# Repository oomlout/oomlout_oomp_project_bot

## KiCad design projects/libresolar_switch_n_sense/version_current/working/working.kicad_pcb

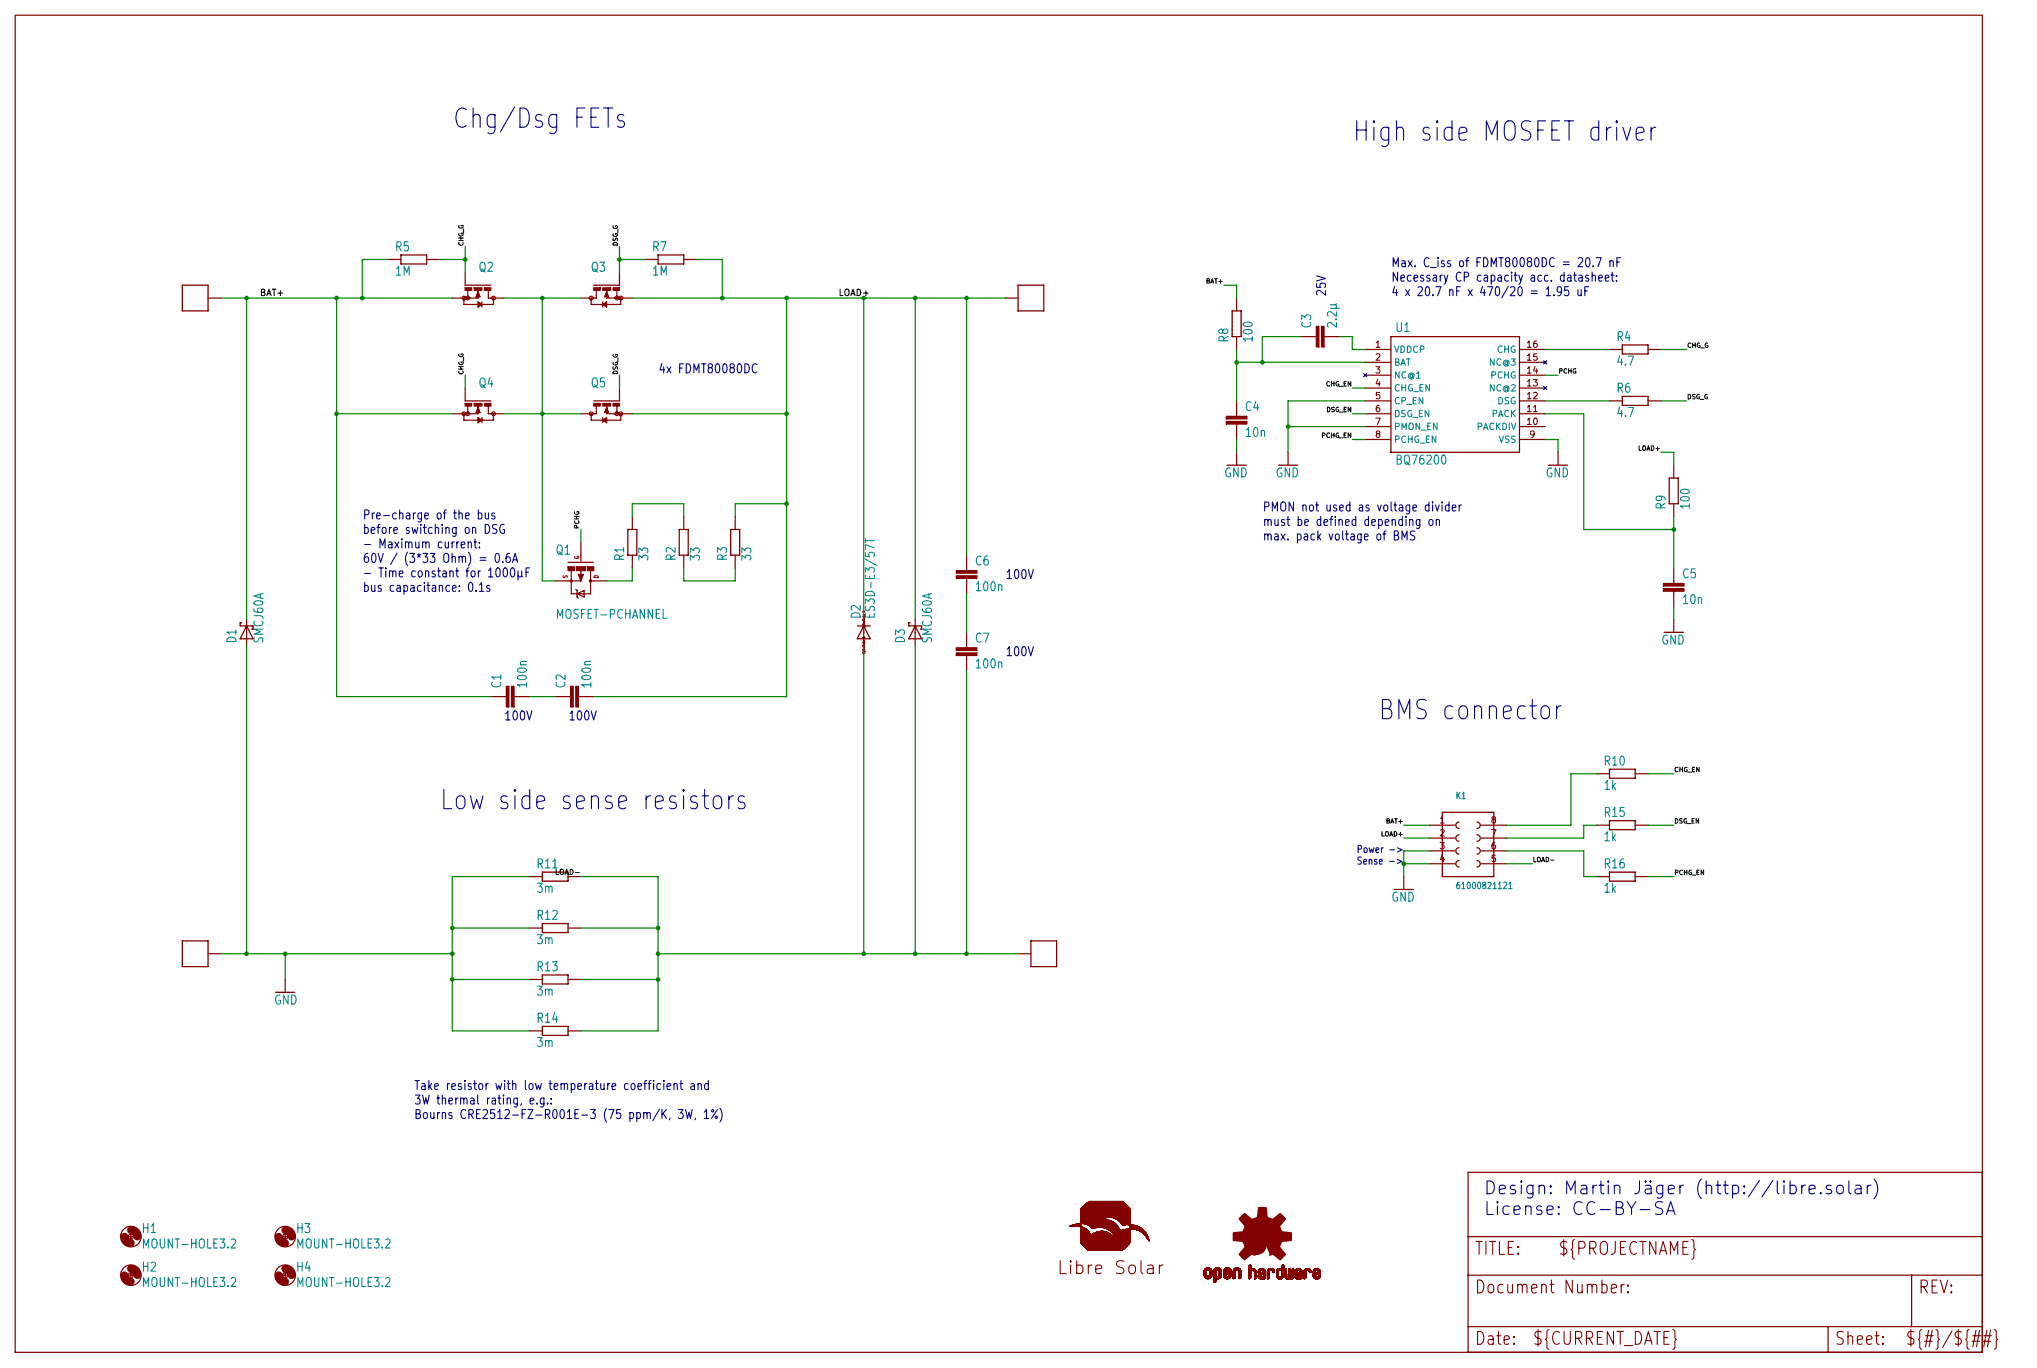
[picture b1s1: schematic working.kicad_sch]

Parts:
BAT+0: WP-BUCF_G; 16PINS_CIR
BAT-0: WP-BUCF_G; 16PINS_CIR
C1, C2, C6, C7: 100n; C0603; MPN 0603B104K500CT
C3: 2.2µ; C0805; MPN 0603B104K500CT
C4, C5: 10n; C0603; MPN GRM188R71H103KA01D.
D1, D3: SMCJ60A; SMC; MPN SMCJ75A
D2: ES3D-E3/57T; SMC; MPN ES3D-E3/57T.
H1, H2, H3, H4: MOUNT-HOLE3.2; 3,2
K1: 61000821121
LOAD+0: WP-BUCF_G; 16PINS_CIR
LOAD-0: WP-BUCF_G; 16PINS_CIR
N1: OSHW-LOGOM; OSHW-LOGO-M
Q1: MOSFET-PCHANNEL; SOT23-3; MPN ZXMP10A13FTA
Q2, Q3, Q4, Q5: FDMT80080DC
R1, R2, R3: 33; R2010; MPN ASC2010-33RFT4
R4, R6: 4.7; R0603; MPN ERJU06F1004V
R5, R7: 1M; R0603; MPN ERJU06F1004V
R8, R9: 100; R0603; MPN MCMR06X1001FTL
R10, R15, R16: 1k; R0603; MPN ERJU06F1004V
R11, R12, R13, R14: 3m; R2512
U1: BQ76200; TSSOP16
U$1: LIBRESOLAR_LOGO

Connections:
BAT+: BAT+0.1, BAT+0.2, BAT+0.3, BAT+0.4, BAT+0.5, BAT+0.6, BAT+0.7, BAT+0.8, BAT+0.9, BAT+0.10, BAT+0.11, BAT+0.12, BAT+0.13, BAT+0.14, BAT+0.15, BAT+0.16, C1.1, D1.C, K1.1, Q2.S, Q4.S, R5.1, R8.2
CHG: R4.1, U1.16 (CHG)
CHGDSG: Q1.2 (S), Q2.D, Q3.D, Q4.D, Q5.D
CHG_EN: R10.2, U1.4 (CHG_EN)
CHG_G: Q2.G, Q4.G, R4.2, R5.2
DSG: R6.1, U1.12 (DSG)
DSG_EN: R15.2, U1.6 (DSG_EN)
DSG_G: Q3.G, Q5.G, R6.2, R7.1
GND: BAT-0.1, BAT-0.2, BAT-0.3, BAT-0.4, BAT-0.5, BAT-0.6, BAT-0.7, BAT-0.8, BAT-0.9, BAT-0.10, BAT-0.11, BAT-0.12, BAT-0.13, BAT-0.14, BAT-0.15, BAT-0.16, C4.2, C5.2, D1.A, K1.3, K1.4, R11.1, R12.1, R13.1, R14.1, U1.5 (CP_EN), U1.7 (PMON_EN), U1.9 (VSS)
LOAD+: C2.2, C6.1, D2.C, D3.C, K1.2, LOAD+0.1, LOAD+0.2, LOAD+0.3, LOAD+0.4, LOAD+0.5, LOAD+0.6, LOAD+0.7, LOAD+0.8, LOAD+0.9, LOAD+0.10, LOAD+0.11, LOAD+0.12, LOAD+0.13, LOAD+0.14, LOAD+0.15, LOAD+0.16, Q3.S, Q5.S, R3.2, R7.2, R9.2
LOAD-: C7.2, D2.A, D3.A, K1.5, LOAD-0.1, LOAD-0.2, LOAD-0.3, LOAD-0.4, LOAD-0.5, LOAD-0.6, LOAD-0.7, LOAD-0.8, LOAD-0.9, LOAD-0.10, LOAD-0.11, LOAD-0.12, LOAD-0.13, LOAD-0.14, LOAD-0.15, LOAD-0.16, R11.2, R12.2, R13.2, R14.2
unnamed: C6.2, C7.1
unnamed: R1.2, R2.2
unnamed: R2.1, R3.1
unnamed: K1.7, R15.1
unnamed: K1.6, R16.1
unnamed: K1.8, R10.1
unnamed: C3.2, U1.1 (VDDCP)
unnamed: C3.1, C4.1, R8.1, U1.2 (BAT)
unnamed: C5.1, R9.1, U1.11 (PACK)
unnamed: C1.2, C2.1
unnamed: Q1.3 (D), R1.1
PCHG: Q1.1 (G), U1.14 (PCHG)
PCHG_EN: R16.2, U1.8 (PCHG_EN)

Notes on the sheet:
100V
BMS connector
Pre-charge of the bus before switching on DSG - Maximum current: 60V / (3*33 Ohm) = 0.6A - Time constant for 1000µF bus capacitance: 0.1s
Max. C_iss of FDMT80080DC = 20.7 nF Necessary CP capacity acc. datasheet: 4 x 20.7 nF x 470/20 = 1.95 uF
Chg/Dsg FETs
Take resistor with low temperature coefficient and 3W thermal rating, e.g.: Bourns CRE2512-FZ-R001E-3 (75 ppm/K, 3W, 1%)
PMON not used as voltage divider must be defined depending on max. pack voltage of BMS
4x FDMT80080DC
Power -> Sense ->
High side MOSFET driver
Low side sense resistors
Design: Martin Jäger (http://libre.solar) License: CC-BY-SA
25V

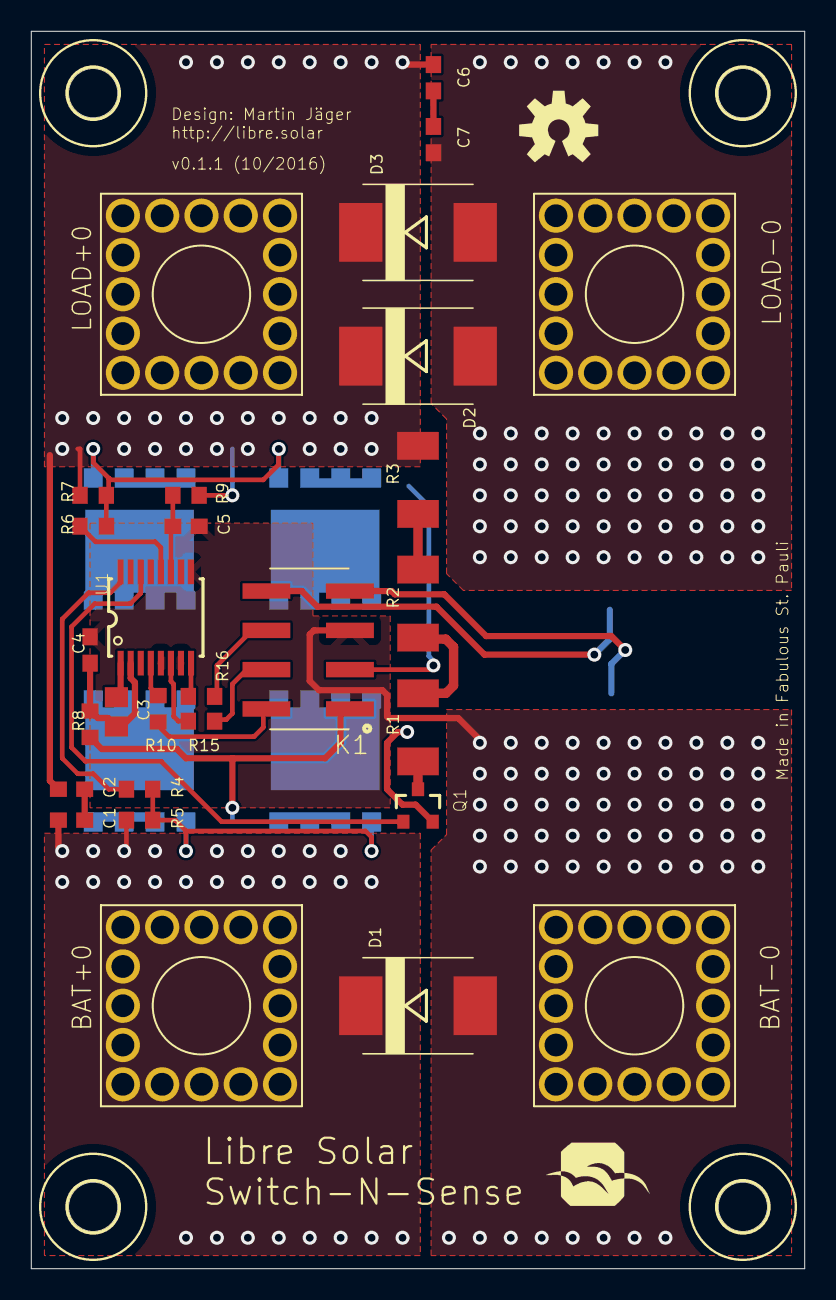
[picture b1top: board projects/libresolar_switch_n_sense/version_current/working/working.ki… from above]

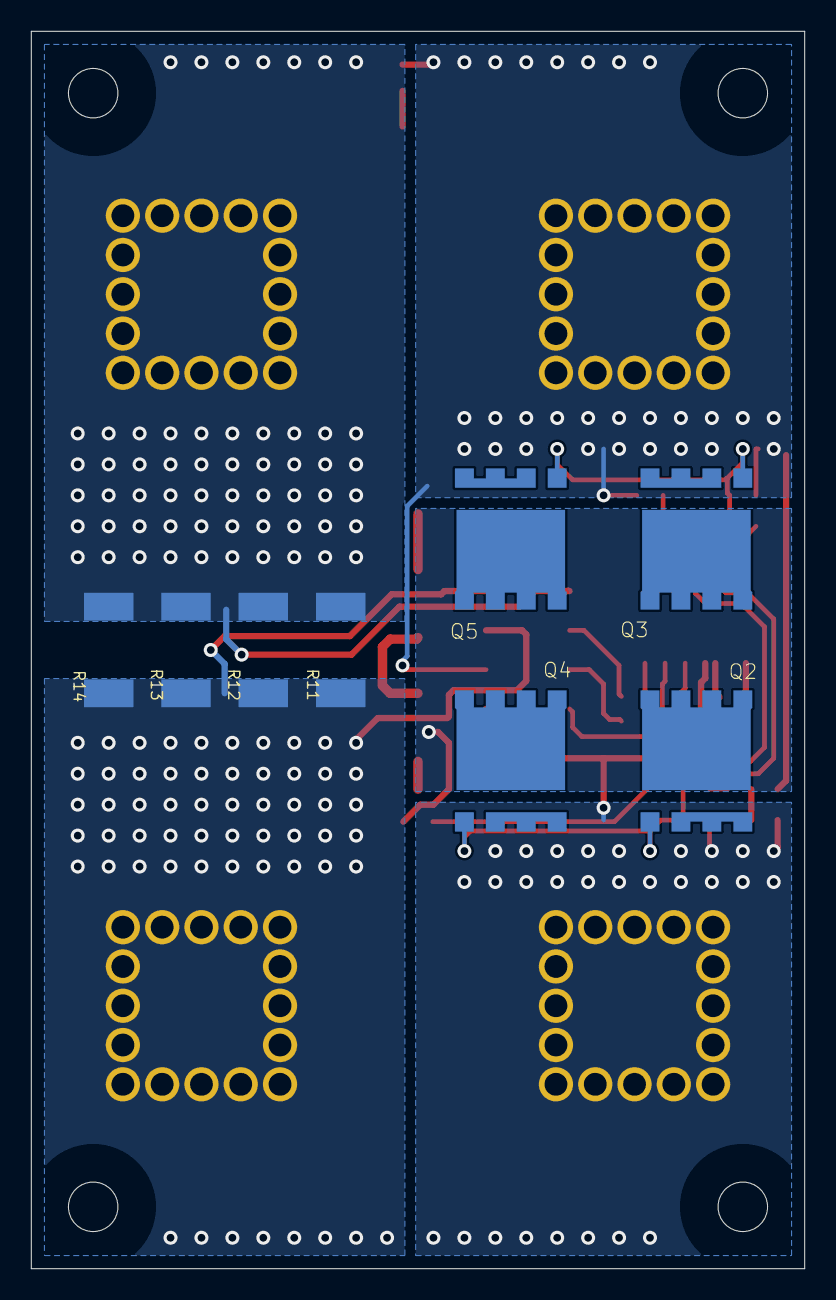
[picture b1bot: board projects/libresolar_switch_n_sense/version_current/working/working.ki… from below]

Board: 2 copper layers, 50.0 x 80.0 mm, 43 parts (8 on the bottom side), 24 nets.

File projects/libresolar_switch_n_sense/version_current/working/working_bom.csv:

"Id";"Designator";"Footprint";"Quantity";"Designation";"Supplier and ref";
1;"U$1";"LIBRESOLAR_LOGO";1;"LIBRESOLAR_LOGO";;;
2;"C1,C2,C6,C7";"C0603";4;"100n";;;
3;"R6,R4";"R0603";2;"4.7";;;
4;"R1,R3,R2";"R2010";3;"33";;;
5;"H4,H2,H3,H1";"3,2";4;"MOUNT-HOLE3.2";;;
6;"C5,C4";"C0603";2;"10n";;;
7;"LOAD+0,BAT+0,BAT-0,LOAD-0";"16PINS_CIR";4;"";;;
8;"R8,R9";"R0603";2;"100";;;
9;"D1,D3";"SMC";2;"SMCJ60A";;;
10;"R7,R5";"R0603";2;"1M";;;
11;"D2";"SMC";1;"ES3D-E3/57T";;;
12;"U1";"TSSOP16";1;"BQ76200";;;
13;"R10,R16,R15";"R0603";3;"1k";;;
14;"K1";"61000821121";1;"61000821121";;;
15;"Q1";"SOT23-3";1;"ZXMP10A13F";;;
16;"N1";"OSHW-LOGO-M";1;"OSHW-LOGOM";;;
17;"C3";"C0805";1;"2.2µ";;;
18;"Q2,Q3,Q5,Q4";"FDMT80080DC";4;"FDMT80080DC";;;
19;"R11,R14,R12,R13";"R2512";4;"3m";;;

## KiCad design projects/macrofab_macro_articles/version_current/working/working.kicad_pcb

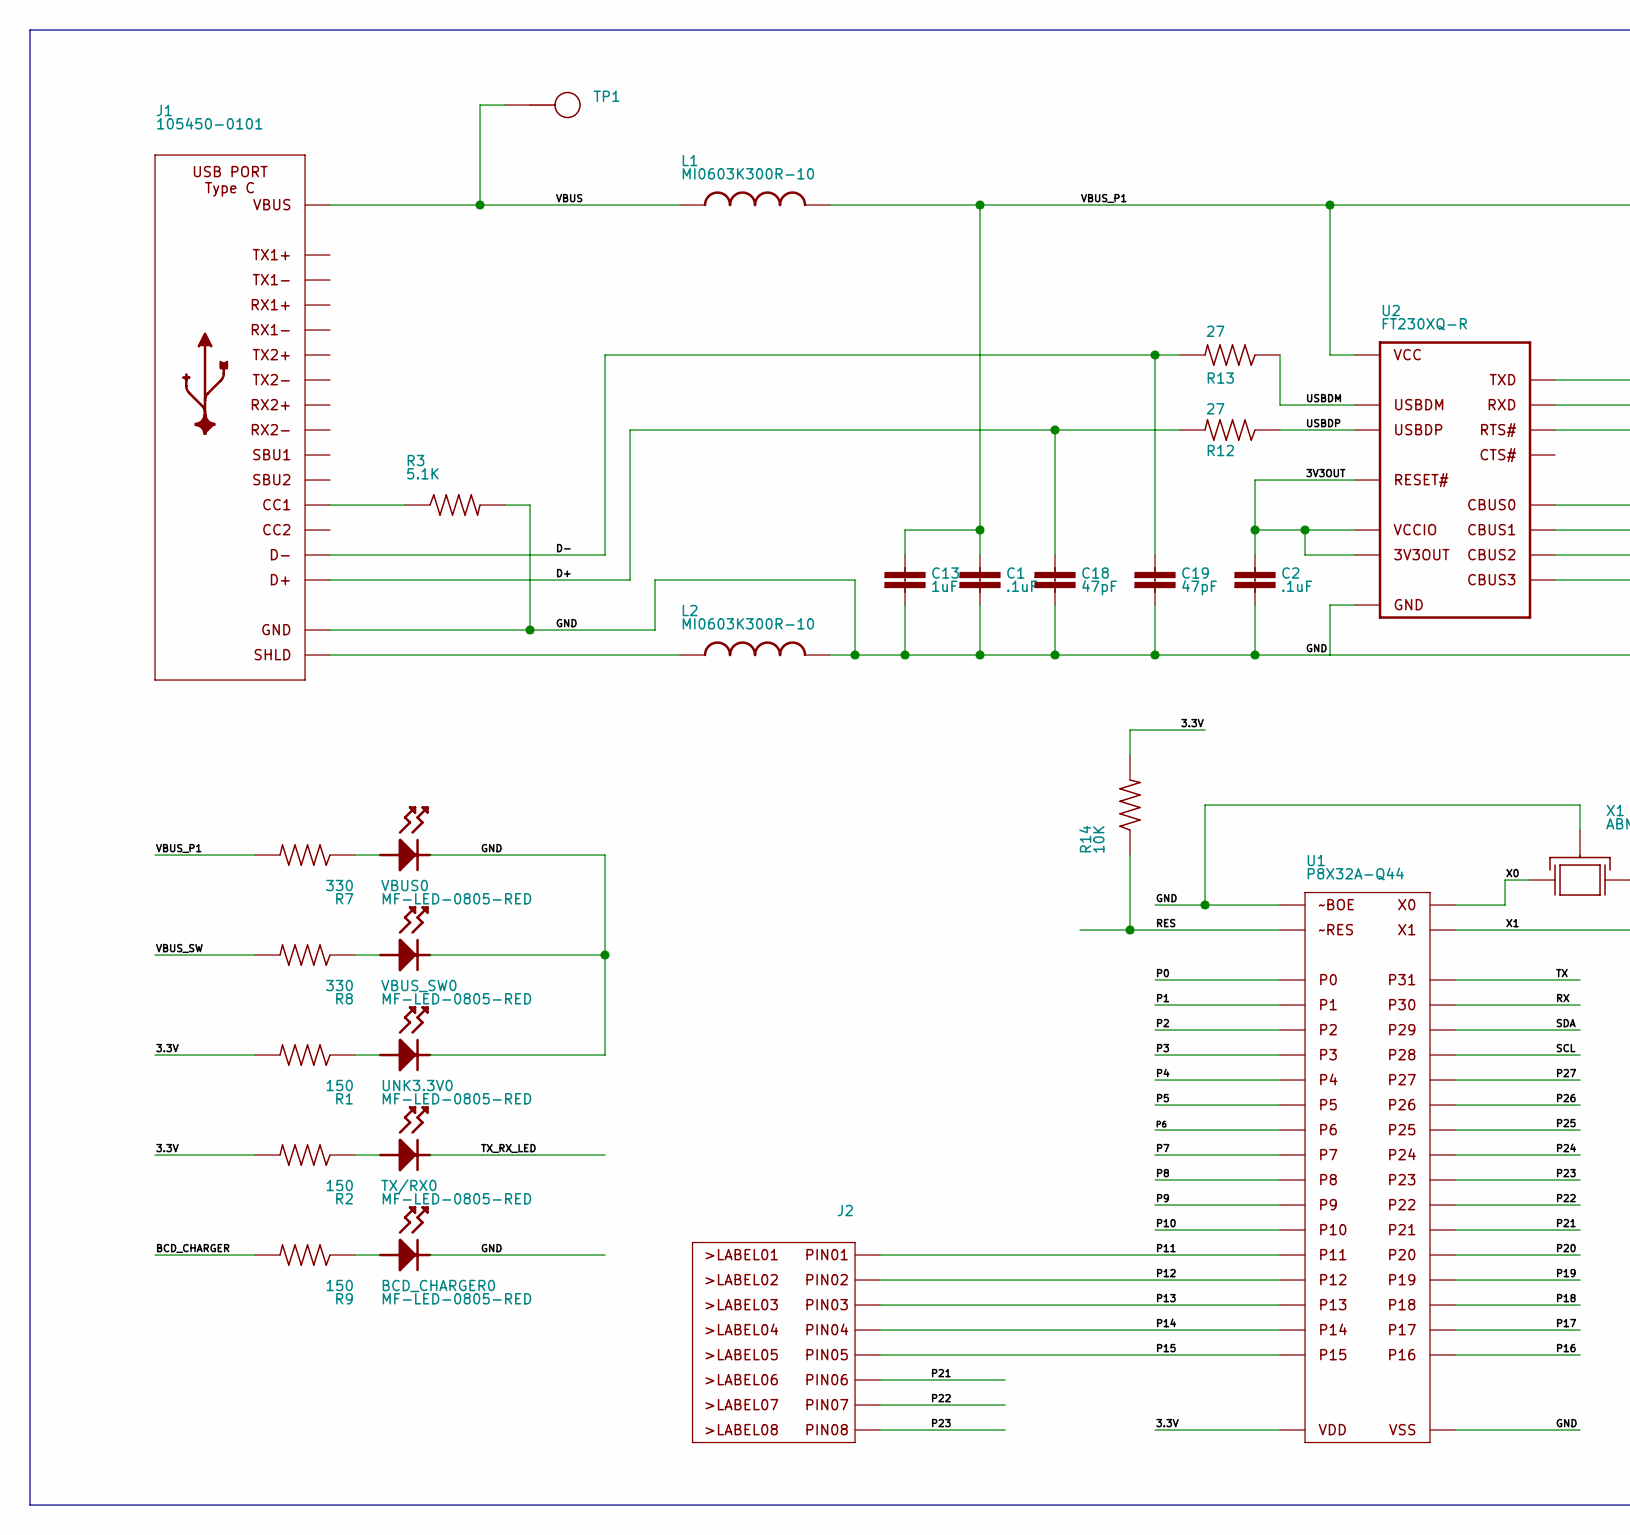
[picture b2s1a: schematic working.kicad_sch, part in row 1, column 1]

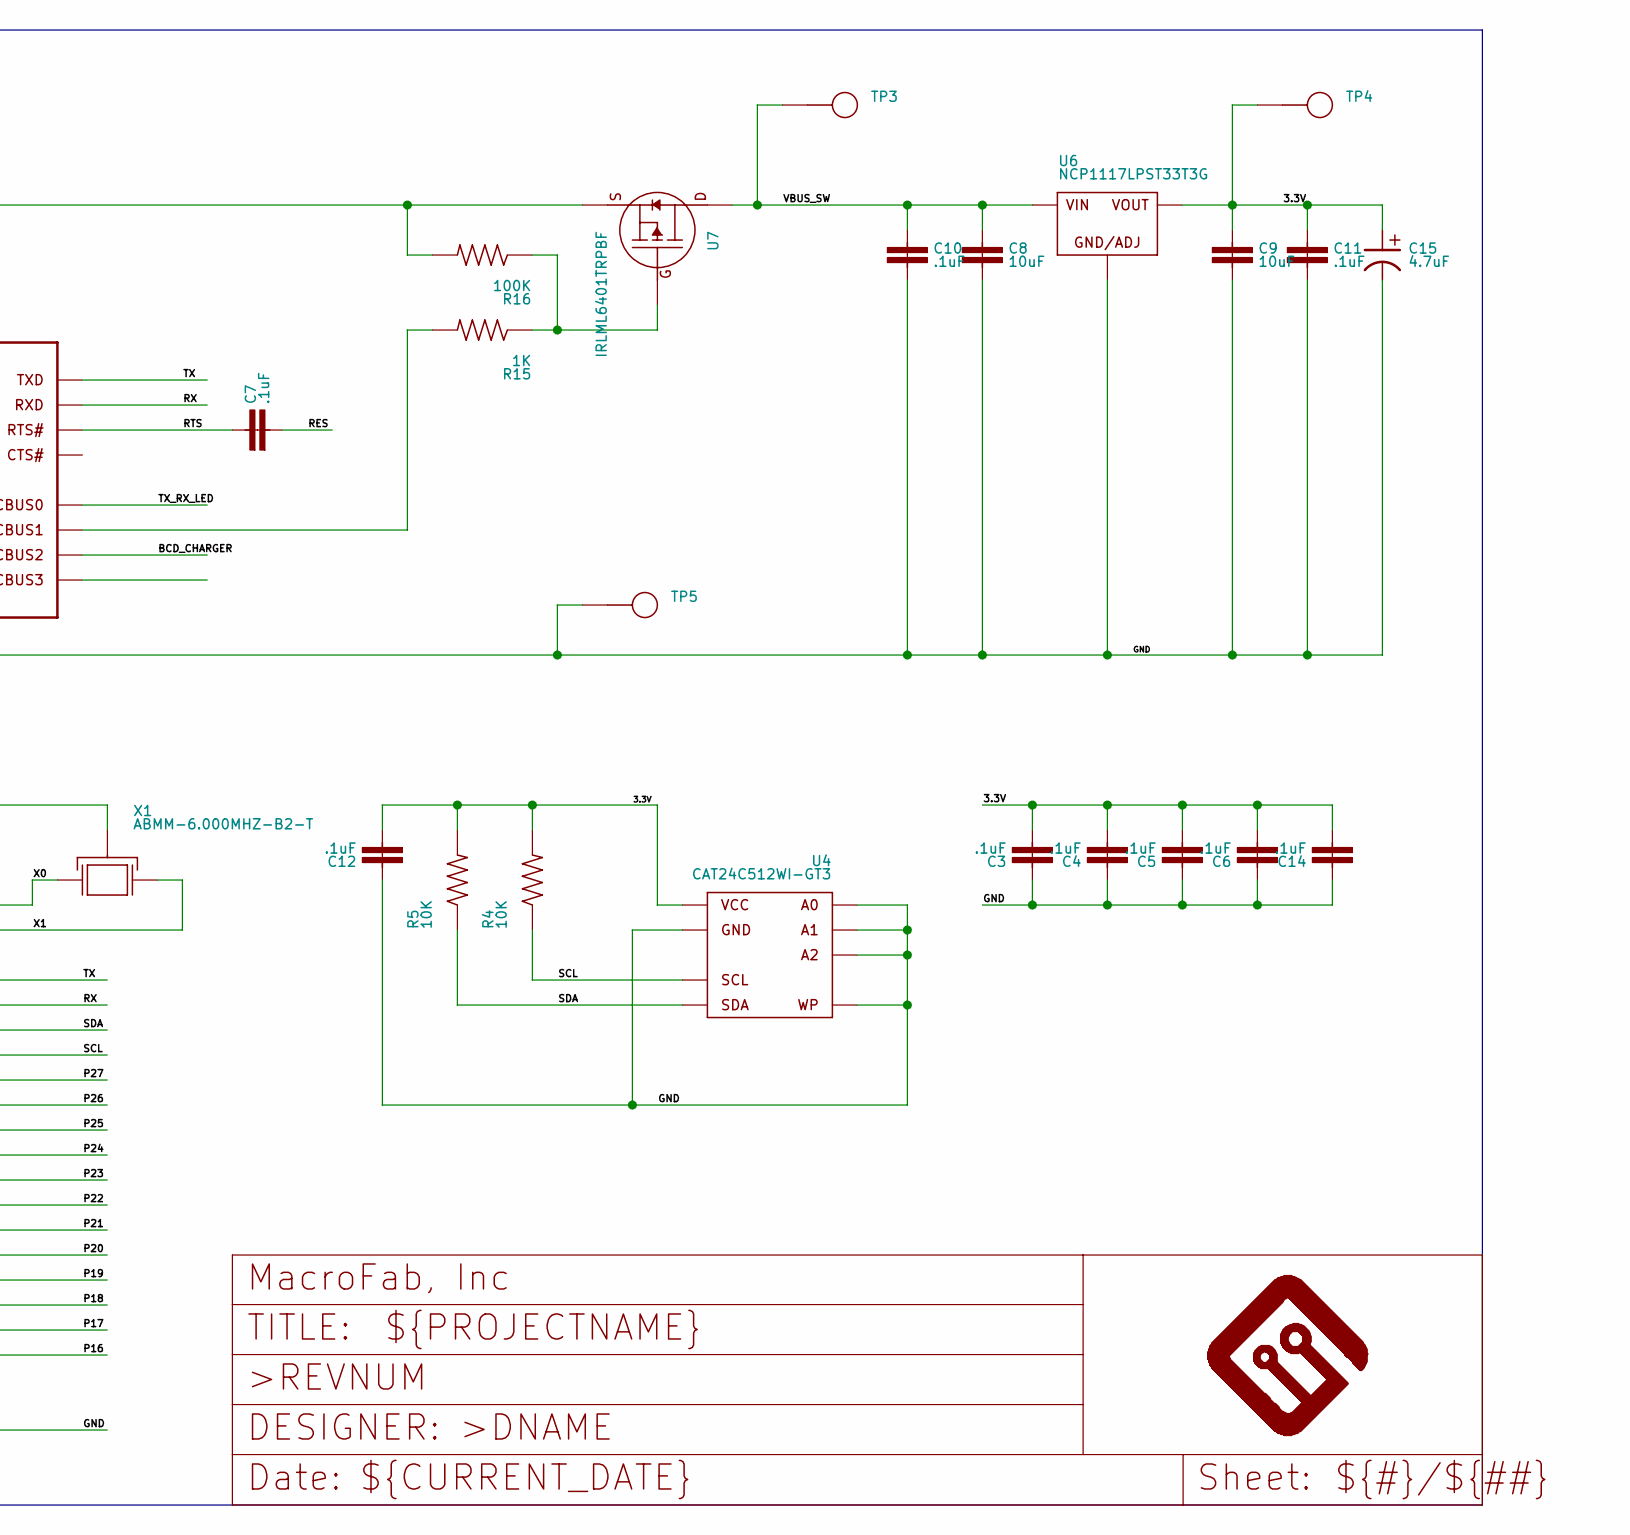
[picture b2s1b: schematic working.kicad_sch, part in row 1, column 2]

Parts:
BCD_CHARGER0: MF-LED-0805-RED; LED_0805
C1, C2, C3, C4, C5, C6, C7, C10, C11, C12, C14: .1uF; 0603
C8, C9: 10uF; 1206
C13: 1uF; 0603
C15: 4.7uF; 5MM_CAP_SMD
C18, C19: 47pF; 0603
FRAME1: MF_FRAMEDEFAULT; MF_FRAME_DEFAULT
J1: 105450-0101; MPN 105450-0101
J2: CON_01X08_2.54MM_PIN_HEADER; 2.54MM_01X08_PIN_HEADER
L1, L2: MI0603K300R-10; 0603
R1, R2, R9: 150; 0603
R3: 5.1K; 0603
R4, R5, R14: 10K; 0603
R7, R8: 330; 0603
R12, R13: 27; 0603
R15: 1K; 0603
R16: 100K; 0603
TP1, TP3, TP4, TP5: TEST_POINT_SINGLE_KEYSTONE_5115-5119; KEYSTONE_5115-5119
TX/RX0: MF-LED-0805-RED; LED_0805
U1: P8X32A-Q44; P8X32A_LQFP-44
U2: FT230XQ-R; FT230X_QFN-16
U4: CAT24C512WI-GT3; SOIC-8_W
U6: NCP1117LPST33T3G; SOT-223-3
U7: IRLML6401TRPBF; SOT-23-3
UNK3.3V0: MF-LED-0805-RED; LED_0805
VBUS0: MF-LED-0805-RED; LED_0805
VBUS_SW0: MF-LED-0805-RED; LED_0805
X1: ABMM-6.000MHZ-B2-T; 7MMX5MM

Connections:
3.3V: C3.2, C4.2, C5.2, C6.2, C9.1, C11.1, C12.2, C14.2, C15.P (POS), R1.2, R2.2, R4.2, R5.2, R14.2, TP4.P$1, U1.8 (VDD), U1.18 (VDD), U1.30 (VDD), U1.40 (VDD), U4.8 (VCC), U6.P$1 (VOUT), U6.P$3 (VOUT)
3V3OUT: C2.1, U2.1 (VCCIO), U2.8 (3V3OUT), U2.9 (RESET#)
BCD_CHARGER: R9.2, U2.5 (CBUS2)
D+: C18.1, J1.A6 (D+), J1.B6 (D+), R12.2
D-: C19.1, J1.A7 (D-), J1.B7 (D-), R13.2
GND: BCD_CHARGER0.CATHODE, C1.2, C2.2, C3.1, C4.1, C5.1, C6.1, C8.2, C9.2, C10.2, C11.2, C12.1, C13.2, C14.1, C15.N (NEG), C18.2, C19.2, J1.A1 (GND), J1.A12 (GND), J1.B1 (GND), J1.B12 (GND), L2.2, R3.2, TP5.P$1, U1.5 (VSS), U1.6 (~BOE), U1.17 (VSS), U1.27 (VSS), U1.39 (VSS), U2.3 (GND), U2.13 (GND), U2.PAD (GND), U4.1 (A0), U4.2 (A1), U4.3 (A2), U4.4 (GND), U4.7 (WP), U6.P$2 (GND/ADJ), UNK3.3V0.CATHODE, VBUS0.CATHODE, VBUS_SW0.CATHODE, X1.P$2 (GND), X1.P$4 (GND)
unnamed: R1.1, UNK3.3V0.ANODE
unnamed: R2.1, TX/RX0.ANODE
unnamed: BCD_CHARGER0.ANODE, R9.1
unnamed: J1.S_T1 (SHLD), J1.S_T2 (SHLD), J1.S_T3 (SHLD), J1.S_T4 (SHLD), L2.1
unnamed: J1.A5 (CC1), R3.1
unnamed: R8.1, VBUS_SW0.ANODE
unnamed: R7.1, VBUS0.ANODE
unnamed: R15.1, R16.1, U7.1 (GATE)
P0: U1.41 (P0)
P1: U1.42 (P1)
P2: U1.43 (P2)
P3: U1.44 (P3)
P4: U1.1 (P4)
P5: U1.2 (P5)
P6: U1.3 (P6)
P7: U1.4 (P7)
P8: U1.9 (P8)
P9: U1.10 (P9)
P10: U1.11 (P10)
P11: J2.1, U1.12 (P11)
P12: J2.2, U1.13 (P12)
P13: J2.3, U1.14 (P13)
P14: J2.4, U1.15 (P14)
P15: J2.5, U1.16 (P15)
P16: U1.19 (P16)
P17: U1.20 (P17)
P18: U1.21 (P18)
P19: U1.22 (P19)
P20: U1.23 (P20)
P21: J2.6, U1.24 (P21)
P22: J2.7, U1.25 (P22)
P23: J2.8, U1.26 (P23)
P24: U1.31 (P24)
P25: U1.32 (P25)
P26: U1.33 (P26)
P27: U1.34 (P27)
PWREN: R15.2, U2.11 (CBUS1)
RES: C7.2, R14.1, U1.7 (~RES)
RTS: C7.1, U2.16 (RTS#)
RX: U1.37 (P30), U2.2 (RXD)
SCL: R4.1, U1.35 (P28), U4.6 (SCL)
SDA: R5.1, U1.36 (P29), U4.5 (SDA)
TX: U1.38 (P31), U2.15 (TXD)
TX_RX_LED: TX/RX0.CATHODE, U2.12 (CBUS0)
USBDM: R13.1, U2.7 (USBDM)
USBDP: R12.1, U2.6 (USBDP)
VBUS: J1.A4 (VBUS), J1.A9 (VBUS), J1.B4 (VBUS), J1.B9 (VBUS), L1.1, TP1.P$1
VBUS_P1: C1.1, C13.1, L1.2, R7.2, R16.2, U2.10 (VCC), U7.2 (SOURCE)
VBUS_SW: C8.1, C10.1, R8.2, TP3.P$1, U6.P$4 (VIN), U7.3 (DRAIN)
X0: U1.29 (X0), X1.P$3 (X1)
X1: U1.28 (X1), X1.P$1 (X0)

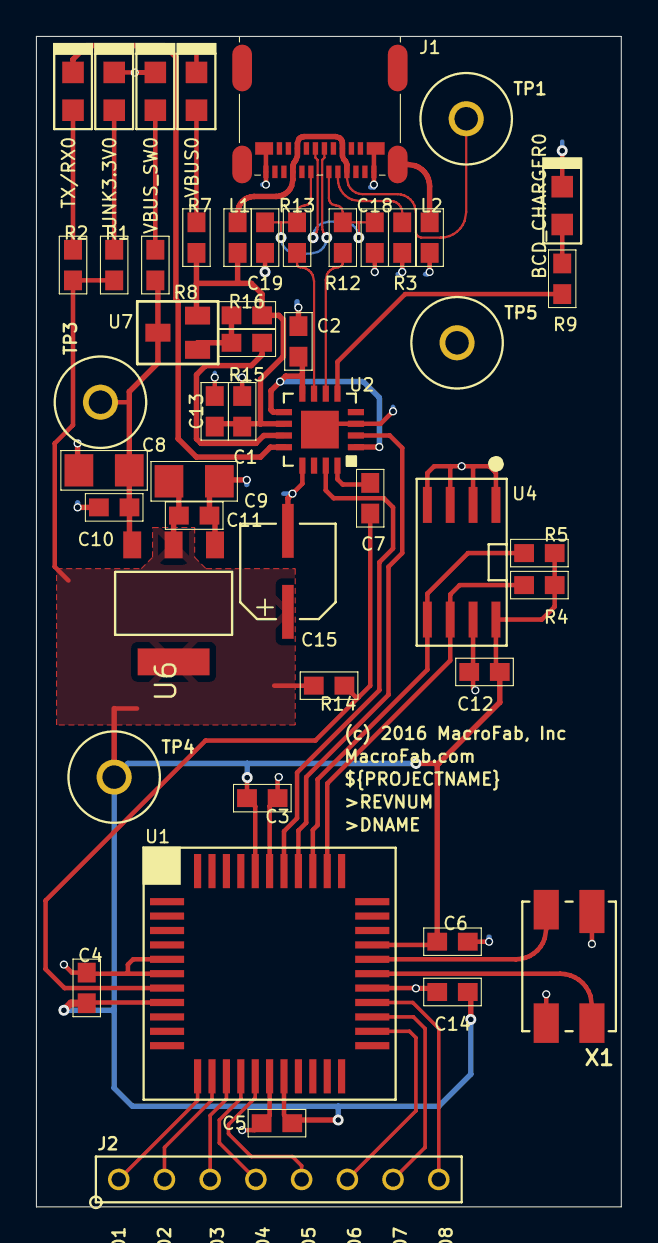
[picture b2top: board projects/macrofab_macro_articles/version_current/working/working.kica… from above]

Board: 2 copper layers, 32.5 x 65.0 mm, 50 parts (0 on the bottom side), 37 nets.

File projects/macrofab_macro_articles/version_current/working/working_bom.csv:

"Id";"Designator";"Footprint";"Quantity";"Designation";"Supplier and ref";
1;"TX/RX0,VBUS_SW0,UNK3.3V0,BCD_CHARGER0,VBUS0";"LED_0805";5;"MF-LED-0805-RED";;;
2;"R2,R1,R9";"0603";3;"150";;;
3;"L1,L2";"0603";2;"MI0603K300R-10";;;
4;"C13";"0603";1;"1uF";;;
5;"R15";"0603";1;"1K";;;
6;"FRAME1";"MF_FRAME_DEFAULT";1;"";;;
7;"C9,C8";"1206";2;"10uF";;;
8;"C19,C18";"0603";2;"47pF";;;
9;"R8,R7";"0603";2;"330";;;
10;"TP5,TP3,TP1,TP4";"KEYSTONE_5115-5119";4;"";;;
11;"X1";"7MMX5MM";1;"ABMM-6.000MHZ-B2-T";;;
12;"J1";"105450-0101";1;"105450-0101";;;
13;"U2";"FT230X_QFN-16";1;"FT230XQ-R";;;
14;"U7";"SOT-23-3";1;"IRLML6401TRPBF";;;
15;"C3,C7,C2,C11,C12,C4,C10,C5,C14,C1,C6";"0603";11;".1uF";;;
16;"J2";"2.54MM_01X08_PIN_HEADER";1;"";;;
17;"U1";"P8X32A_LQFP-44";1;"P8X32A-Q44";;;
18;"C15";"5MM_CAP_SMD";1;"4.7uF";;;
19;"R13,R12";"0603";2;"27";;;
20;"R14,R4,R5";"0603";3;"10K";;;
21;"R3";"0603";1;"5.1K";;;
22;"U6";"SOT-223-3";1;"NCP1117LPST33T3G";;;
23;"R16";"0603";1;"100K";;;
24;"U4";"SOIC-8_W";1;"CAT24C512WI-GT3";;;

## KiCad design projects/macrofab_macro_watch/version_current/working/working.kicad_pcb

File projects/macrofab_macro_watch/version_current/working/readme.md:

# Macro_Watch by MacroFab  
This is a harvested standardized copy of a project from github.  
The original project can be found at:  
https://github.com/MacroFab/Macro_Watch  
Please consult that link for additional, details, files, and license information.  
Note: It was auto harvested and if the original repo had more than one board file or anything out of the ordinary the files here are likely not representative.

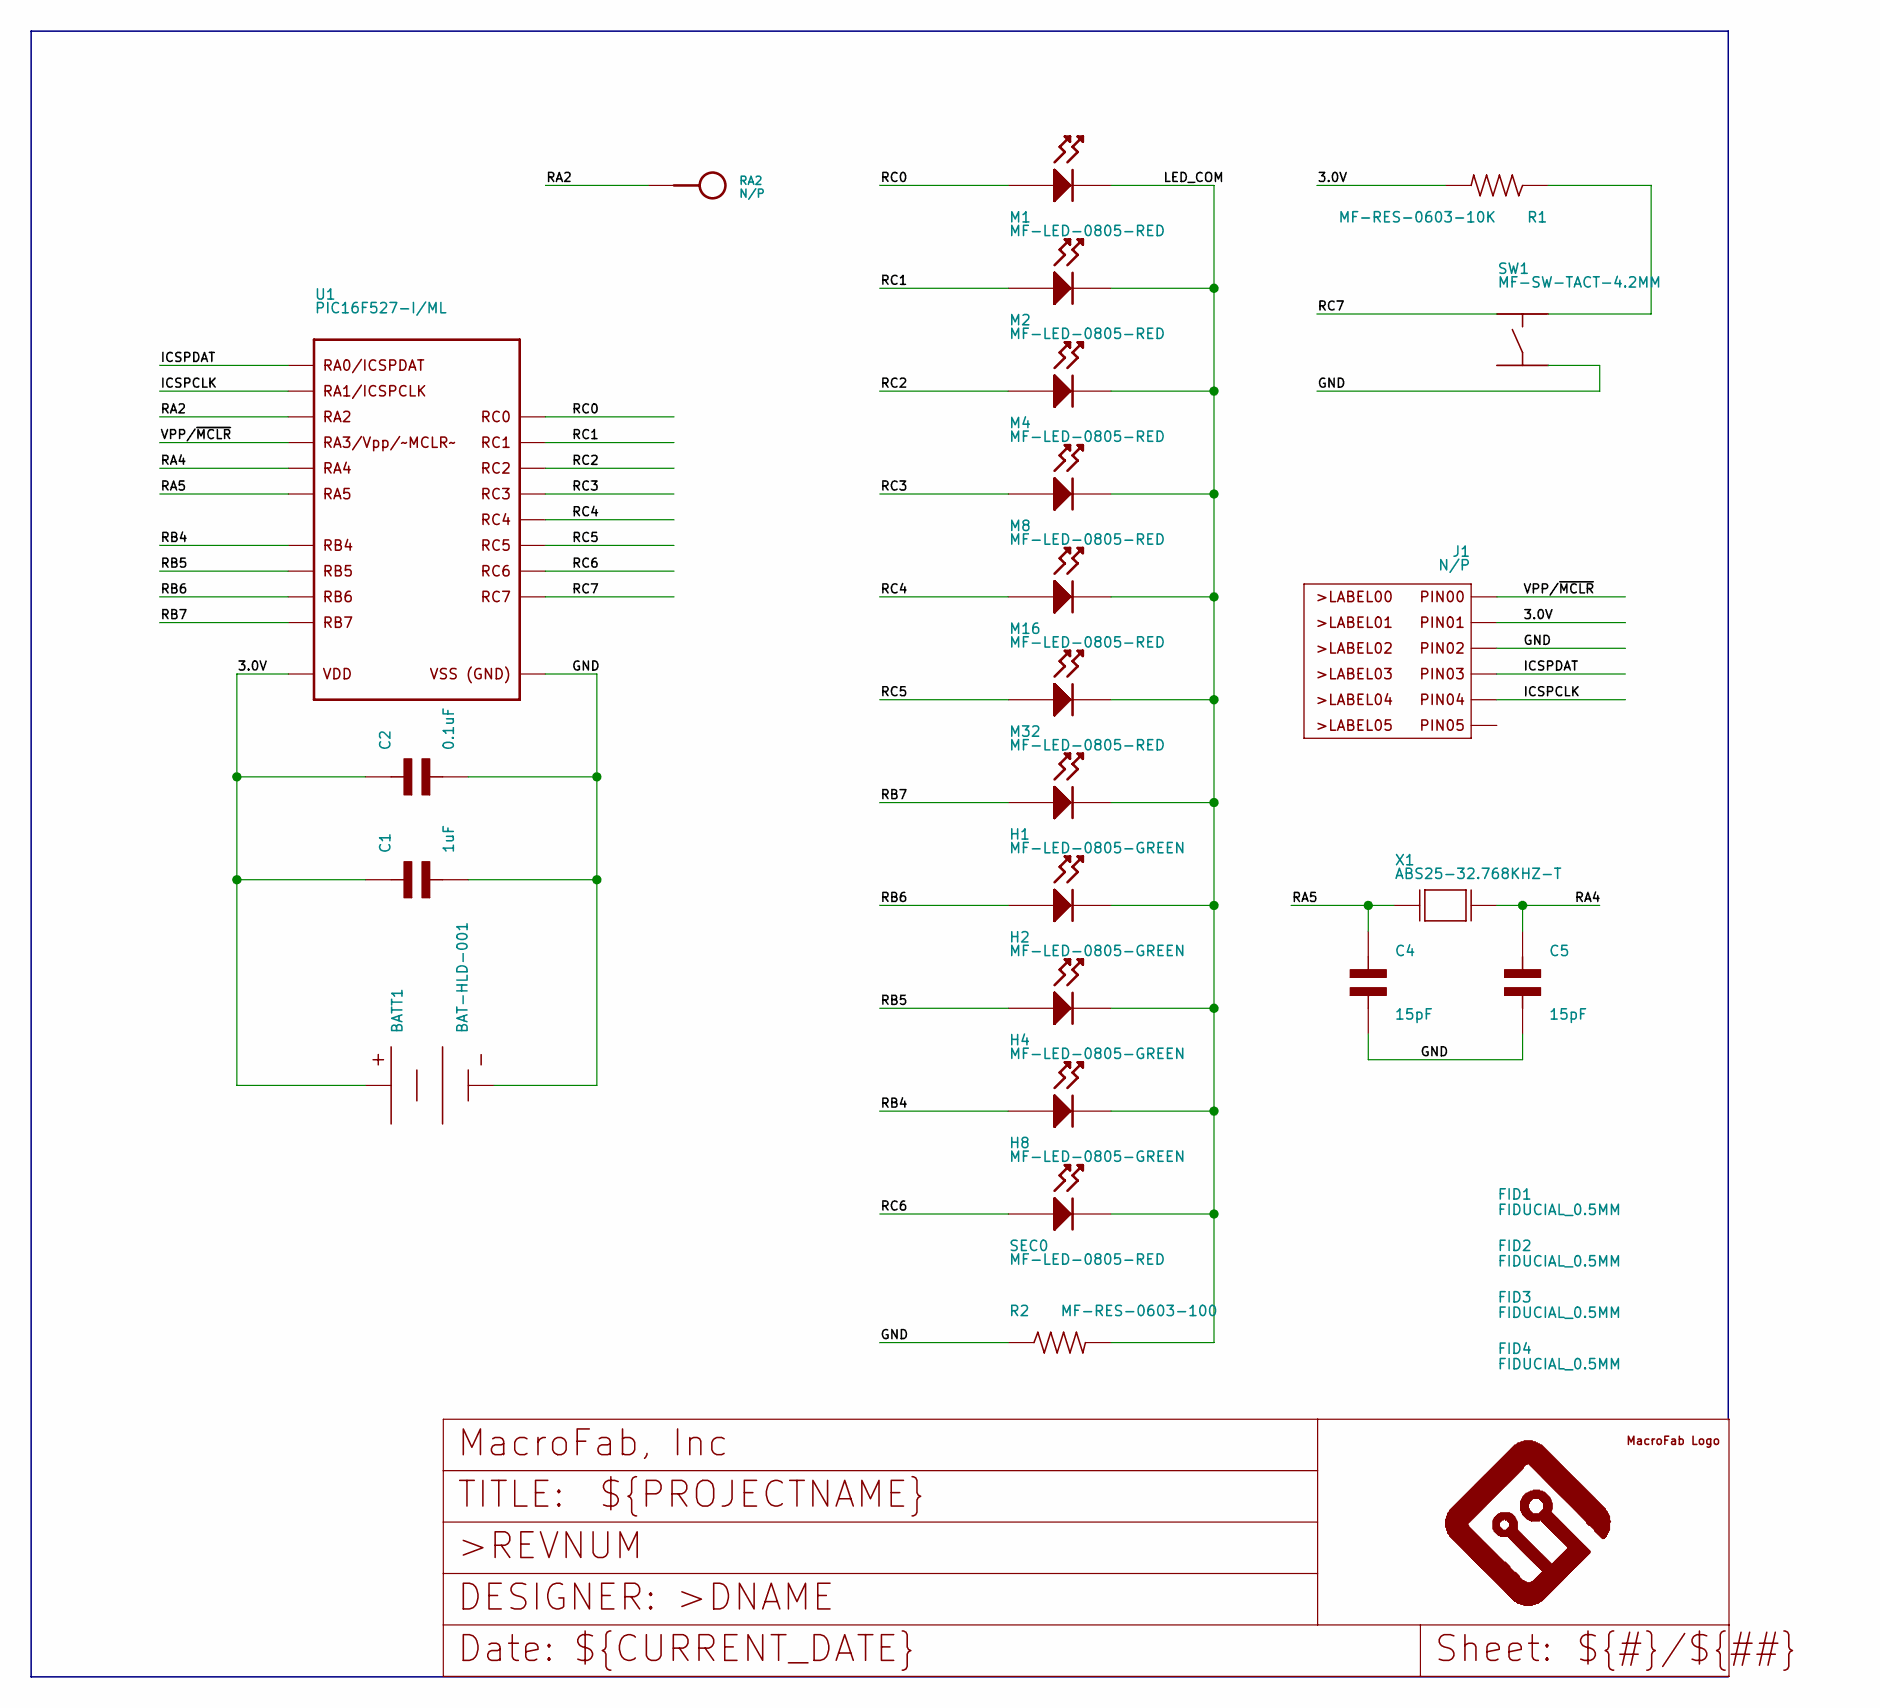
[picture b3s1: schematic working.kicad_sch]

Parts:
BATT1: BAT-HLD-001
C1: 1uF; C0603
C2: 0.1uF; C0603
C4, C5: 15pF; C0603
FID1, FID2, FID3, FID4: FIDUCIAL_0.5MM
FRAME1: MF_FRAMEDEFAULT; MF_FRAME_DEFAULT
H1, H2, H4, H8: MF-LED-0805-GREEN; LED0805
J1: N/P; PTH_2.54MM_01X06
M1, M2, M4, M8, M16, M32: MF-LED-0805-RED; LED0805
R1: MF-RES-0603-10K; R0603
R2: MF-RES-0603-100; R0603
RA2: N/P; ROUND_TP
SEC0: MF-LED-0805-RED; LED0805
SW1: MF-SW-TACT-4.2MM; TACT4.2MM
U1: PIC16F527-I/ML; QFN20
U$1: MF_LOGOLOGO_SMALL; MF_LOGO_SMALL
X1: ABS25-32.768KHZ-T; ABS25_SERIES

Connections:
3.0V: BATT1.POS_0 (POS), BATT1.POS_1 (POS), C1.P$1, C2.P$1, J1.P$2 (PIN1), R1.P$2, U1.P$18 (VDD)
GND: BATT1.NEG_0 (NEG), C1.P$2, C2.P$2, C4.P$2, C5.P$2, J1.P$3 (PIN2), R2.P$1, SW1.P$4, U1.P$17 (GND)
ICSPCLK: J1.P$5 (PIN4), U1.P$15 (RA1/ICSPCLK)
ICSPDAT: J1.P$4 (PIN3), U1.P$16 (RA0/ICSPDAT)
LED_COM: H1.CATHODE, H2.CATHODE, H4.CATHODE, H8.CATHODE, M1.CATHODE, M2.CATHODE, M4.CATHODE, M8.CATHODE, M16.CATHODE, M32.CATHODE, R2.P$2, SEC0.CATHODE
unnamed: R1.P$1, SW1.P$2
RA2: RA2.P$1, U1.P$14 (RA2)
RA4: C5.P$1, U1.P$20 (RA4), X1.4 (X1)
RA5: C4.P$1, U1.P$19 (RA5), X1.1 (X0)
RB4: H8.ANODE, U1.P$10 (RB4)
RB5: H4.ANODE, U1.P$9 (RB5)
RB6: H2.ANODE, U1.P$8 (RB6)
RB7: H1.ANODE, U1.P$7 (RB7)
RC0: M1.ANODE, U1.P$13 (RC0)
RC1: M2.ANODE, U1.P$12 (RC1)
RC2: M4.ANODE, U1.P$11 (RC2)
RC3: M8.ANODE, U1.P$4 (RC3)
RC4: M16.ANODE, U1.P$3 (RC4)
RC5: M32.ANODE, U1.P$2 (RC5)
RC6: SEC0.ANODE, U1.P$5 (RC6)
RC7: SW1.P$1, U1.P$6 (RC7)
VPP/~MCLR: J1.P$1 (PIN0), U1.P$1 (RA3/VPP/~MCLR)

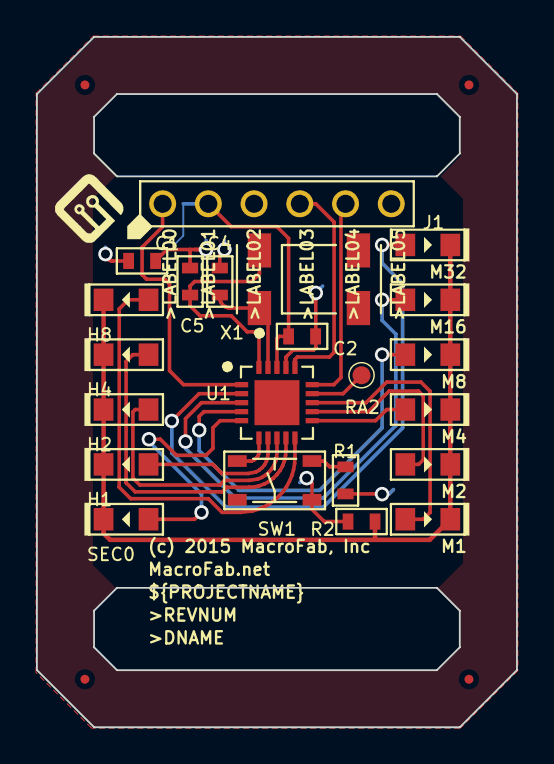
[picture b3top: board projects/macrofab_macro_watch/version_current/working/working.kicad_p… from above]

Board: 2 copper layers, 26.7 x 38.4 mm, 29 parts (1 on the bottom side), 22 nets.

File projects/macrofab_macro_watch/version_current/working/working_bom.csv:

"Id";"Designator";"Footprint";"Quantity";"Designation";"Supplier and ref";
1;"M4,M16,M32,M1,M8,SEC0,M2";"LED0805";7;"MF-LED-0805-RED";;;
2;"H1,H4,H2,H8";"LED0805";4;"MF-LED-0805-GREEN";;;
3;"X1";"ABS25_SERIES";1;"ABS25-32.768KHZ-T";;;
4;"RA2";"ROUND_TP";1;"N/P";;;
5;"C4,C5";"C0603";2;"15pF";;;
6;"J1";"PTH_2.54MM_01X06";1;"N/P";;;
7;"R2";"R0603";1;"MF-RES-0603-100";;;
8;"R1";"R0603";1;"MF-RES-0603-10K";;;
9;"U$1";"MF_LOGO_SMALL";1;"MF_LOGOLOGO_SMALL";;;
10;"C2";"C0603";1;"0.1uF";;;
11;"FID1,FID2,FID3,FID4";"FIDUCIAL_0.5MM";4;"FIDUCIAL_0.5MM";;;
12;"FRAME1";"MF_FRAME_DEFAULT";1;"MF_FRAMEDEFAULT";;;
13;"SW1";"TACT4.2MM";1;"MF-SW-TACT-4.2MM";;;
14;"C1";"C0603";1;"1uF";;;
15;"U1";"QFN20";1;"PIC16F527-I/ML";;;
16;"BATT1";"BAT-HLD-001";1;"BAT-HLD-001";;;

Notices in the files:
parts and their libraries:
(c) 2016 MacroFab, Inc
(c) 2015 MacroFab, Inc
(c) 2013 MacroFab, Inc
